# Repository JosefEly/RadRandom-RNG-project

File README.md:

# RadRandom-RNG-project
Schematics and code for a hardware RNG project

This project works using a smoke detector AM-241 source and a reverse-biased photodiode. When an alpha particle hits the detector, this registers as a voltage spike which is converted to a digital signal by a comparator (with hysterisis to avoid turning one detection event into two). An Arduino measures the time between two sets of pulses - if A is greater than B, it's a 1, if A < B, it's a 0, and if they are equal, it tries again recursively. Because the generator can only generate so many bits at a time, these bits are generated and then cached, and each roll pulls from the cached file. Because radioactive decay is random at the quantum level, the bits should be too. A Python verison of the NIST statistical test suite thought the bits were in fact random. I attached the results here.

https://github.com/ozel/DIY_particle_detector/wiki

This was used for the alpha detector in the project.

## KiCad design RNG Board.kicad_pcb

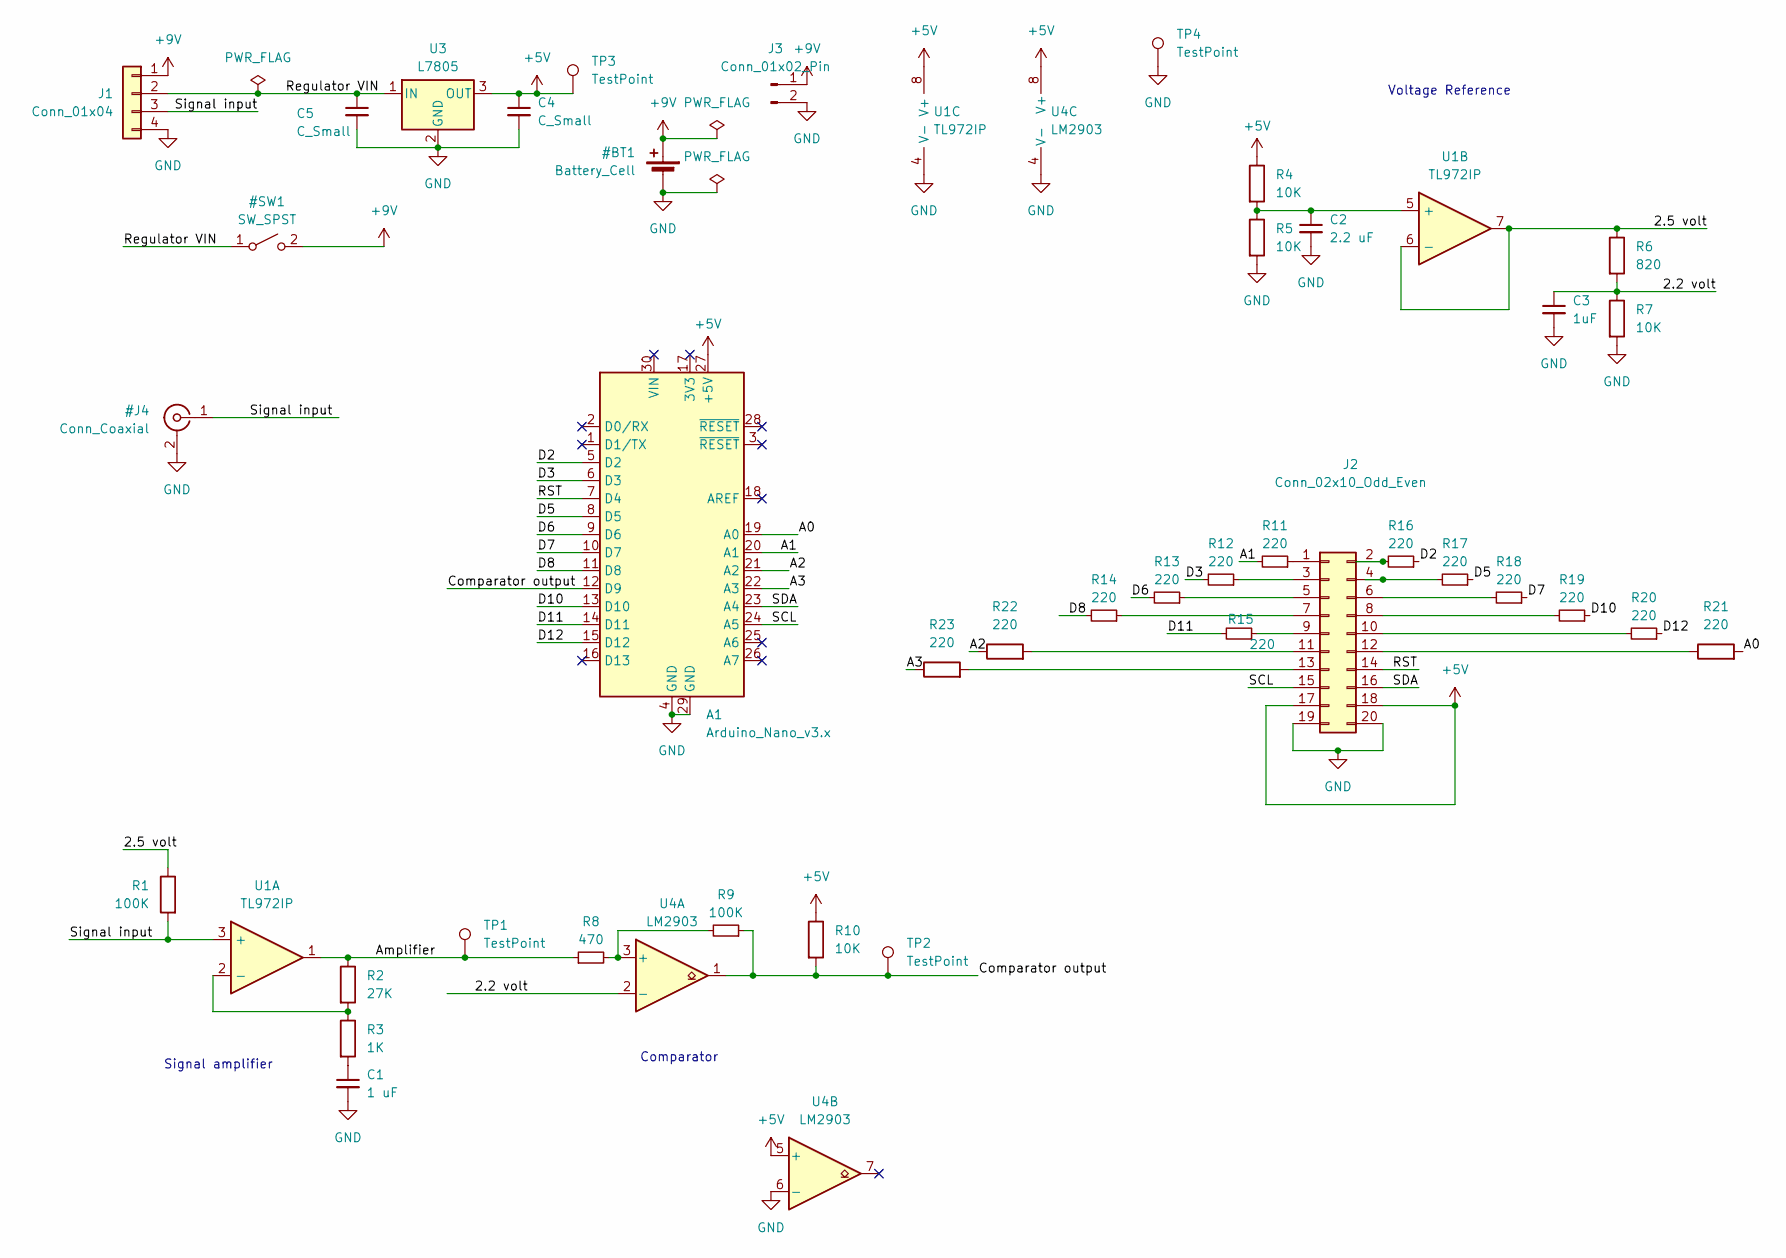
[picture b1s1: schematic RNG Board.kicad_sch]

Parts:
A1: Arduino_Nano_v3.x; Arduino_Nano
C1: 1 uF; C_Disc_D4.3mm_W1.9mm_P5.00mm
C2: 2.2 uF; C_Disc_D4.3mm_W1.9mm_P5.00mm
C3: 1uF; C_Disc_D4.3mm_W1.9mm_P5.00mm
C4, C5: C_Small; C_Disc_D4.3mm_W1.9mm_P5.00mm
J1: Conn_01x04; PinHeader_1x04_P2.54mm_Vertical
J2: Conn_02x10_Odd_Even; PinHeader_2x10_P2.54mm_Vertical
J3: Conn_01x02_Pin; SolderWire-0.5sqmm_1x02_P4.6mm_D0.9mm_OD2.1mm
R1, R9: 100K; R_Axial_DIN0207_L6.3mm_D2.5mm_P7.62mm_Horizontal
R2: 27K; R_Axial_DIN0207_L6.3mm_D2.5mm_P7.62mm_Horizontal
R3: 1K; R_Axial_DIN0207_L6.3mm_D2.5mm_P7.62mm_Horizontal
R4, R5, R7, R10: 10K; R_Axial_DIN0207_L6.3mm_D2.5mm_P7.62mm_Horizontal
R6: 820; R_Axial_DIN0207_L6.3mm_D2.5mm_P7.62mm_Horizontal
R8: 470; R_Axial_DIN0207_L6.3mm_D2.5mm_P7.62mm_Horizontal
R11, R12, R13, R14, R15, R16, R17, R18, R19, R20, R21, R22, R23: 220; R_Axial_DIN0207_L6.3mm_D2.5mm_P7.62mm_Horizontal
TP1, TP2, TP3, TP4: TestPoint; TestPoint_THTPad_1.5x1.5mm_Drill0.7mm
U1: TL972IP; DIP-8_W7.62mm
U3: L7805; TO-220-3_Vertical
U4: LM2903; DIP-8_W7.62mm

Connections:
+5V: A1.27 (+5V), C4.1, J2.17, J2.18, R4.1, R10.1, TP3.1, U1.8 (V+), U3.3 (OUT), U4.5 (+), U4.8 (V+)
/2.2 volt: C3.1, R6.2, R7.1, U4.2 (-)
/2.5 volt: R1.1, R6.1, U1.6 (-), U1.7
/A0: A1.19 (A0), R21.2
/A1: A1.20 (A1), R11.2
/A2: A1.21 (A2), R22.1
/A3: A1.22 (A3), R23.1
/Amplifier: R2.1, R8.1, TP1.1, U1.1
/Comparator output: A1.12 (D9), R9.1, R10.2, TP2.1, U4.1
/D2: A1.5 (D2), R16.1
/D3: A1.6 (D3), R12.2
/D5: A1.8 (D5), R17.1
/D6: A1.9 (D6), R13.2
/D7: A1.10 (D7), R18.1
/D8: A1.11 (D8), R14.2
/D10: A1.13 (D10), R19.1
/D11: A1.14 (D11), R15.2
/D12: A1.15 (D12), R20.1
/RST: A1.7 (D4), J2.14
/SCL: A1.24 (A5), J2.15
/SDA: A1.23 (A4), J2.16
unnamed: C1.1, R3.2
unnamed: J2.1, R11.1
unnamed: J2.2, R16.2
unnamed: J2.3, R12.1
unnamed: J2.4, R17.2
unnamed: J2.5, R13.1
unnamed: J2.6, R18.2
unnamed: J2.7, R14.1
unnamed: J2.8, R19.2
unnamed: J2.9, R15.1
unnamed: J2.10, R20.2
unnamed: J2.11, R22.2
unnamed: J2.12, R21.1
unnamed: J2.13, R23.2
unnamed: R2.2, R3.1, U1.2 (-)
unnamed: C2.1, R4.2, R5.1, U1.5 (+)
unnamed: R8.2, R9.2, U4.3 (+)

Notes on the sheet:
Signal amplifier
Voltage Reference
Comparator

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
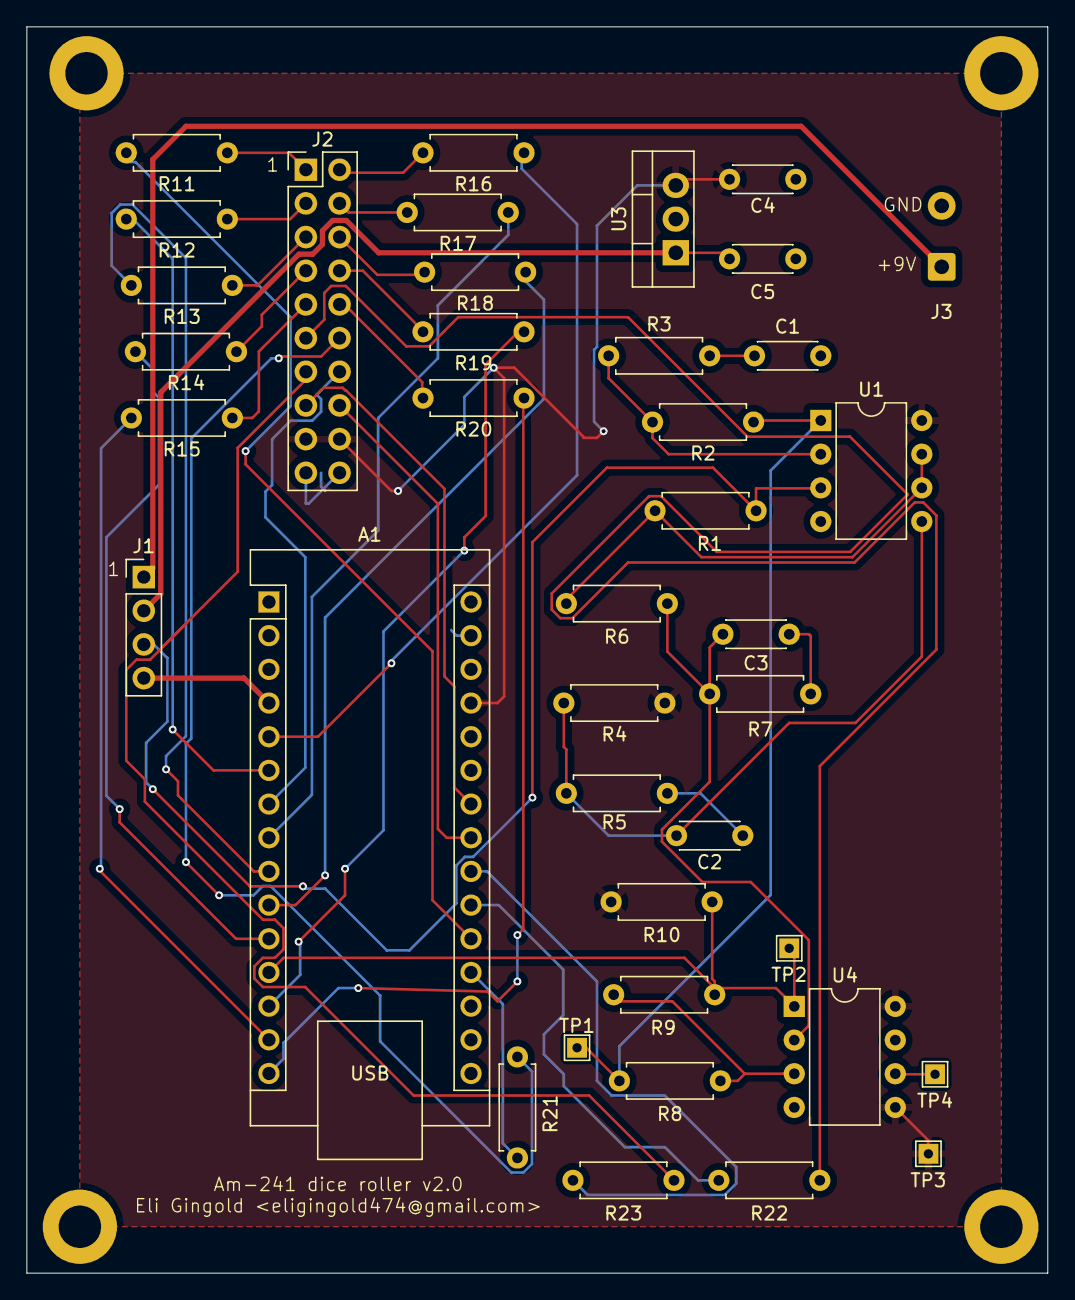
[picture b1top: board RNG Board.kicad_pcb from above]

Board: 2 copper layers, 77.0 x 94.0 mm, 39 parts (0 on the bottom side), 42 nets.
